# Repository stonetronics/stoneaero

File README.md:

# stoneaero
Flight controller + transmitter hardware using Arduino Nano, NRF24L01, MPU6050, etc

basic transmitter/receiver code is contained in these folders:

* transmitter
  * basic joystick operation
  * throttle on potentiometer

* receiver
  * basic servo signal forwarding from rf module
  * automatic throttle cut and circular descent when there is no signal received for 1.5s

more advanced functions are contained in receevur/trunsmeetur

* hw
  * eagle files for both pcbs
  * receevur
    * ATmega328p
    * 7 servo channels
    * 3S lipo voltage measurement
    * current measurement
    * MPU9250/MPU6050 header
    * NRF24L01+PA+LNA module
  * trunsmeetur
    * Arduino Mega
    * 16x2 generic lcd
    * buttons for lcd menu
    * NRF24L01+PA+LNA module
    * pinheaders for connecting joysticks, switches etc
    * designed to replace the electronics on a "modelcraft N-6" transmitter

* receevur
  * servo signals
    * airbrake mode for ailerons
  * current/voltage reporting

* trunsmeetur
  * lcd display
    * current/voltage report display
    * joystick settings
  * controls for servo signals

feel free to edit

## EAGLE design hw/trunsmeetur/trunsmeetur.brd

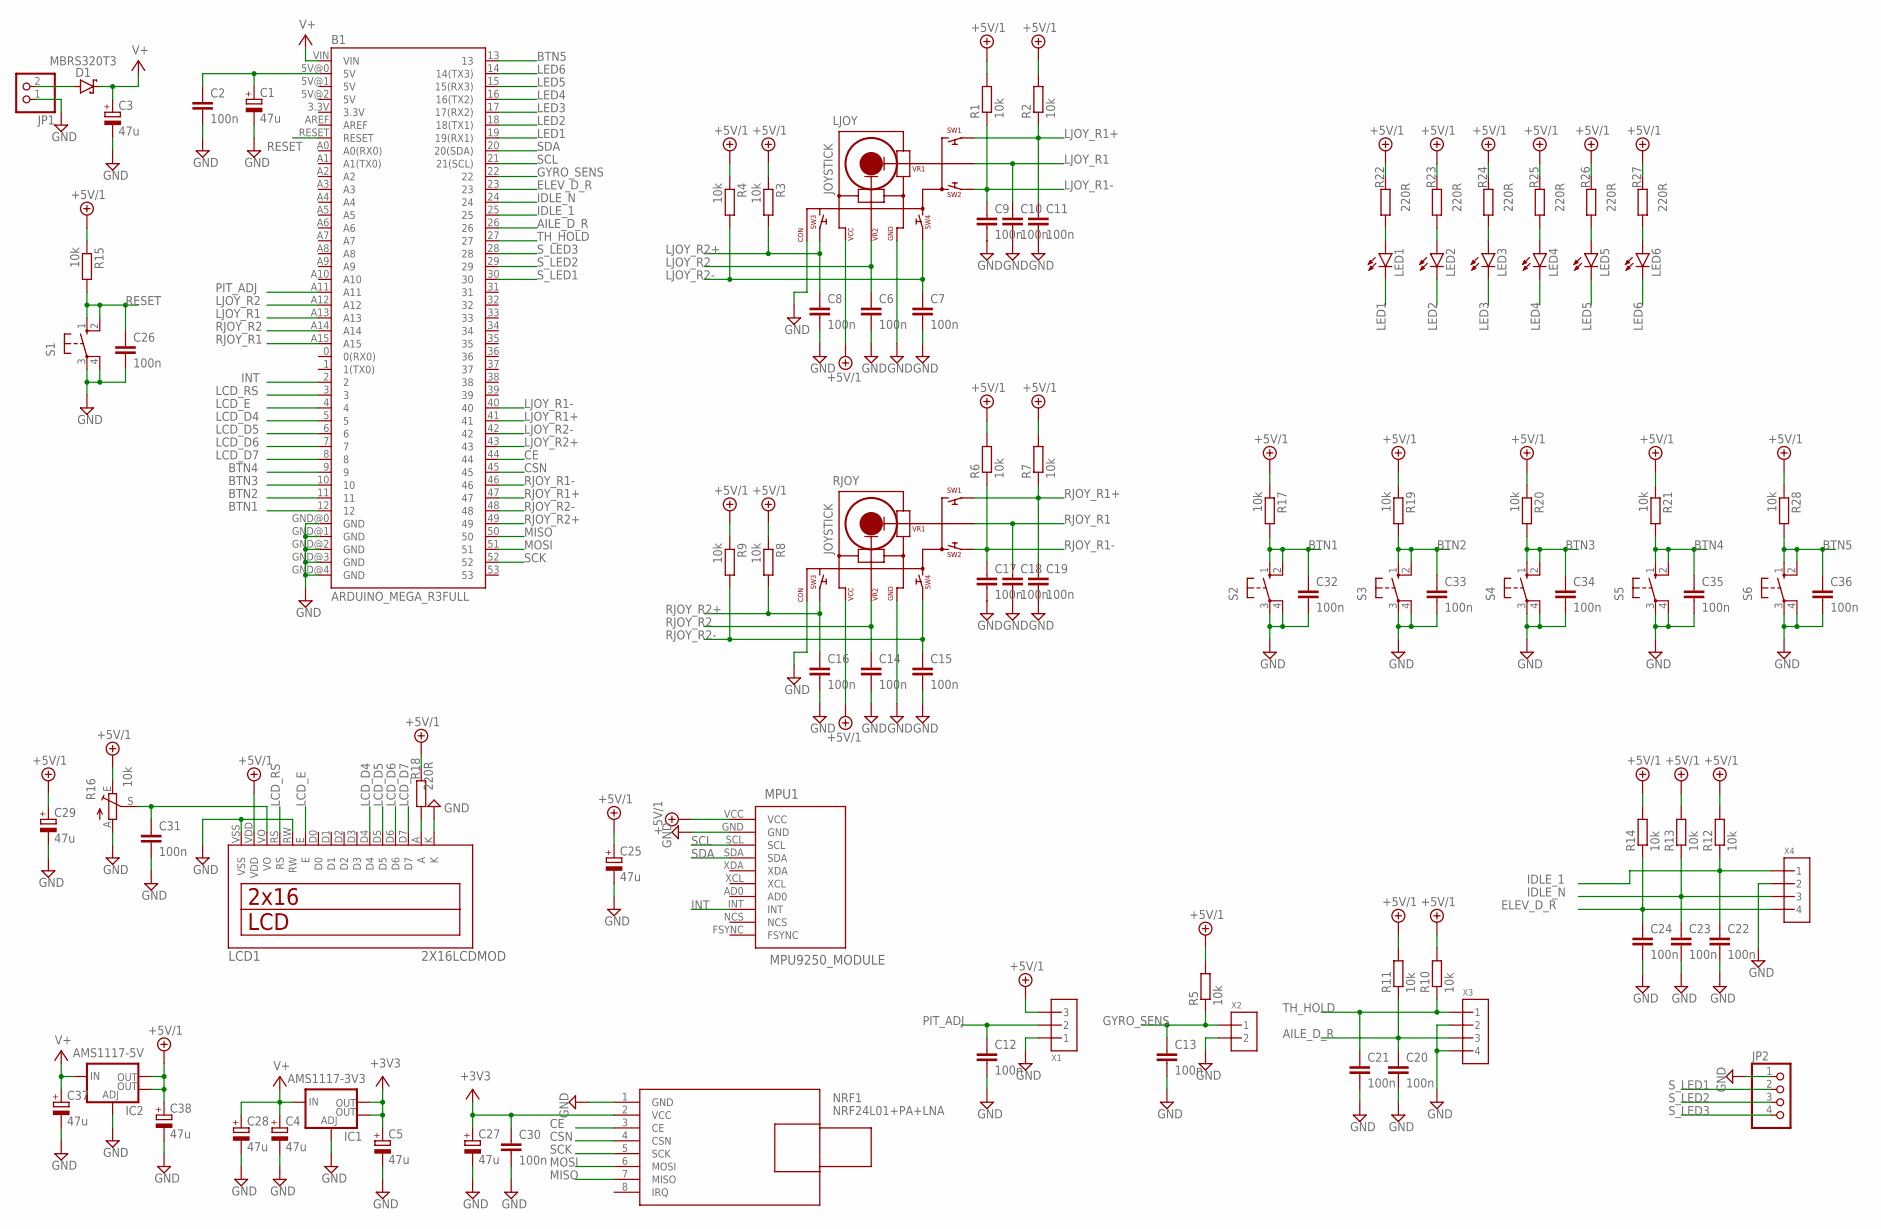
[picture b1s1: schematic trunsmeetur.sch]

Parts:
B1: ARDUINO_MEGA_R3FULL; ARDUINO_MEGA
C1, C3, C4, C5, C25, C27, C28, C29, C37, C38: 47u; 153CLV-0605
C2, C6, C7, C8, C9, C10, C11, C12, C13, C14, C15, C16, C17, C18, C19, C20, C21, C22, C23, C24, C26, C30, C31, C32, C33, C34, C35, C36: 100n; C0805
D1: MBRS320T3; SMC
IC1: AMS1117-3V3; SOT223
IC2: AMS1117-5V; SOT223
JP1: PINHD-1X2; 1X02
JP2: PINHD-1X4; 1X04
LCD1: 2X16LCDMOD; LCD16X2MOD
LED1, LED2, LED3, LED4, LED5, LED6: LEDCHIPLED_0805; CHIPLED_0805
LJOY: JOYSTICK; JOYSTICKCONNECTOR
MPU1: MPU9250_MODULE
NRF1: NRF24L01+PA+LNA; WIRELESS-NRF24L01-PA-EXT
R1, R2, R3, R4, R5, R6, R7, R8, R9, R10, R11, R12, R13, R14, R15, R17, R19, R20, R21, R28: 10k; M0805
R16: 10k; CA9V
R18, R22, R23, R24, R25, R26, R27: 220R; M0805
RJOY: JOYSTICK; JOYSTICKCONNECTOR
S1, S2, S3, S4, S5, S6: 10-XX; B3F-10XX
X1: 3PIN; 3PINCONNECTOR
X2: 2PIN; 2PINCONNECTOR
X3, X4: 4PIN; 4PINCONNECTOR

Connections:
+3V3: C5.+, C27.+, C30.1, IC1.2 (OUT), IC1.4 (OUT), NRF1.2 (VCC)
+5V/1: C25.+, C29.+, C38.+, IC2.2 (OUT), IC2.4 (OUT), LCD1.VDD, LJOY.VCC, MPU1.VCC, R1.2, R2.2, R3.1, R4.1, R5.2, R6.2, R7.2, R8.1, R9.1, R10.2, R11.2, R12.2, R13.2, R14.2, R15.1, R16.E, R17.1, R18.1, R19.1, R20.1, R21.1, R22.1, R23.1, R24.1, R25.1, R26.1, R27.1, R28.1, RJOY.VCC, X1.3
AILE_D_R: B1.26, C20.1, R11.1, X3.3
BTN1: B1.12, C32.1, R17.2, S2.1 (S), S2.2 (S1)
BTN2: B1.11, C33.1, R19.2, S3.1 (S), S3.2 (S1)
BTN3: B1.10, C34.1, R20.2, S4.1 (S), S4.2 (S1)
BTN4: B1.9, C35.1, R21.2, S5.1 (S), S5.2 (S1)
BTN5: B1.13, C36.1, R28.2, S6.1 (S), S6.2 (S1)
CE: B1.44, NRF1.3 (CE)
CSN: B1.45, NRF1.4 (CSN)
ELEV_D_R: B1.23, C24.1, R14.1, X4.4
GND: B1.GND@0 (GND), B1.GND@1 (GND), B1.GND@2 (GND), B1.GND@3 (GND), B1.GND@4 (GND), C1.-, C2.2, C3.-, C4.-, C5.-, C6.2, C7.2, C8.2, C9.2, C10.2, C11.2, C12.2, C13.2, C14.2, C15.2, C16.2, C17.2, C18.2, C19.2, C20.2, C21.2, C22.2, C23.2, C24.2, C25.-, C26.2, C27.-, C28.-, C29.-, C30.2, C31.2, C32.2, C33.2, C34.2, C35.2, C36.2, C37.-, C38.-, IC1.1 (ADJ), IC2.1 (ADJ), JP1.1, JP2.1, LCD1.K, LCD1.RW, LCD1.VSS, LJOY.CON, LJOY.GND, MPU1.GND, NRF1.1 (GND), R16.A, RJOY.CON, RJOY.GND, S1.3, S1.4 (P1), S2.3, S2.4 (P1), S3.3, S3.4 (P1), S4.3, S4.4 (P1), S5.3, S5.4 (P1), S6.3, S6.4 (P1), X1.1, X2.2, X3.2, X3.4, X4.2
GYRO_SENS: B1.22, C13.1, R5.1, X2.1
IDLE_1: B1.25, C22.1, R12.1, X4.1
IDLE_N: B1.24, C23.1, R13.1, X4.3
INT: B1.2, MPU1.INT
LCD_D4: B1.5, LCD1.D4
LCD_D5: B1.6, LCD1.D5
LCD_D6: B1.7, LCD1.D6
LCD_D7: B1.8, LCD1.D7
LCD_E: B1.4, LCD1.E
LCD_RS: B1.3, LCD1.RS
LED1: B1.19 (19(RX1)), LED1.C
LED2: B1.18 (18(TX1)), LED2.C
LED3: B1.17 (17(RX2)), LED3.C
LED4: B1.16 (16(TX2)), LED4.C
LED5: B1.15 (15(RX3)), LED5.C
LED6: B1.14 (14(TX3)), LED6.C
LJOY_R1: B1.A13, C10.1, LJOY.VR1
LJOY_R1+: B1.41, C11.1, LJOY.SW1, R2.1
LJOY_R1-: B1.40, C9.1, LJOY.SW2, R1.1
LJOY_R2: B1.A12, C6.1, LJOY.VR2
LJOY_R2+: B1.43, C8.1, LJOY.SW3, R3.2
LJOY_R2-: B1.42, C7.1, LJOY.SW4, R4.2
MISO: B1.50, NRF1.7 (MISO)
MOSI: B1.51, NRF1.6 (MOSI)
unnamed: C31.1, LCD1.VO, R16.S
unnamed: D1.A, JP1.2
unnamed: LCD1.A, R18.2
unnamed: LED1.A, R22.2
unnamed: LED2.A, R23.2
unnamed: LED3.A, R24.2
unnamed: LED4.A, R25.2
unnamed: LED5.A, R26.2
unnamed: LED6.A, R27.2
unnamed: B1.5V@0 (5V), C1.+, C2.1
PIT_ADJ: B1.A11, C12.1, X1.2
RESET: B1.RESET, C26.1, R15.2, S1.1 (S), S1.2 (S1)
RJOY_R1: B1.A15, C18.1, RJOY.VR1
RJOY_R1+: B1.47, C19.1, R7.1, RJOY.SW1
RJOY_R1-: B1.46, C17.1, R6.1, RJOY.SW2
RJOY_R2: B1.A14, C14.1, RJOY.VR2
RJOY_R2+: B1.49, C16.1, R8.2, RJOY.SW3
RJOY_R2-: B1.48, C15.1, R9.2, RJOY.SW4
SCK: B1.52, NRF1.5 (SCK)
SCL: B1.21 (21(SCL)), MPU1.SCL
SDA: B1.20 (20(SDA)), MPU1.SDA
S_LED1: B1.30, JP2.2
S_LED2: B1.29, JP2.3
S_LED3: B1.28, JP2.4
TH_HOLD: B1.27, C21.1, R10.1, X3.1
V+: B1.VIN, C3.+, C4.+, C28.+, C37.+, D1.C, IC1.3 (IN), IC2.3 (IN)

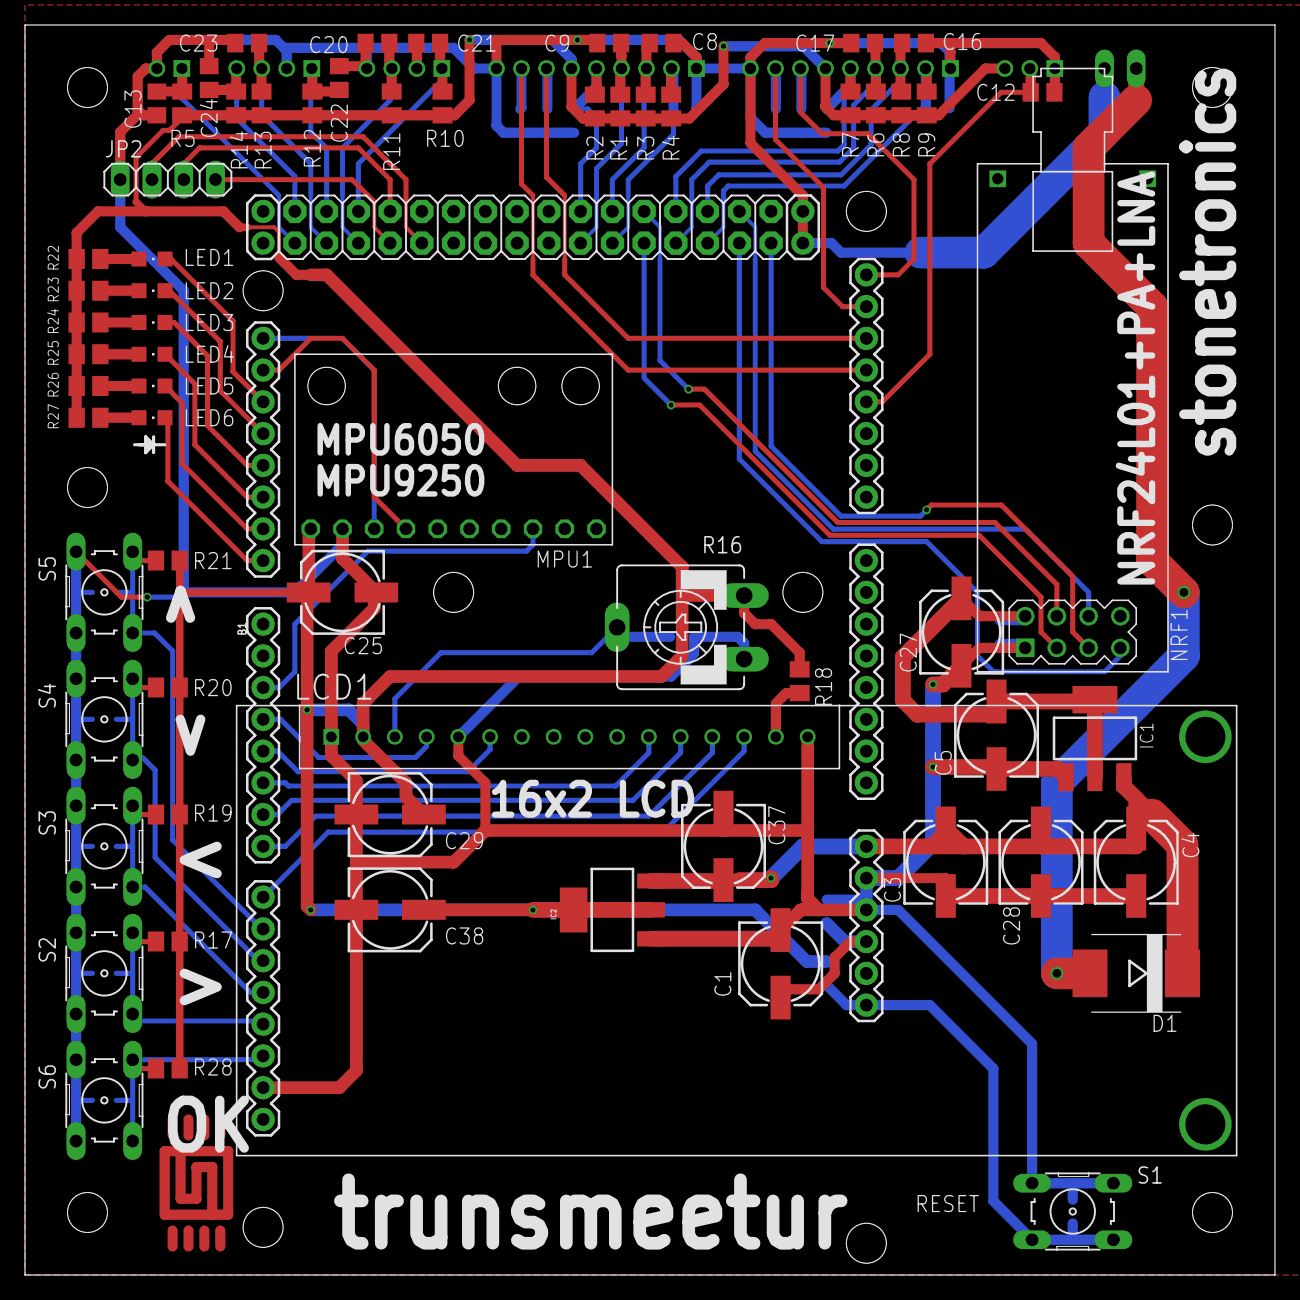
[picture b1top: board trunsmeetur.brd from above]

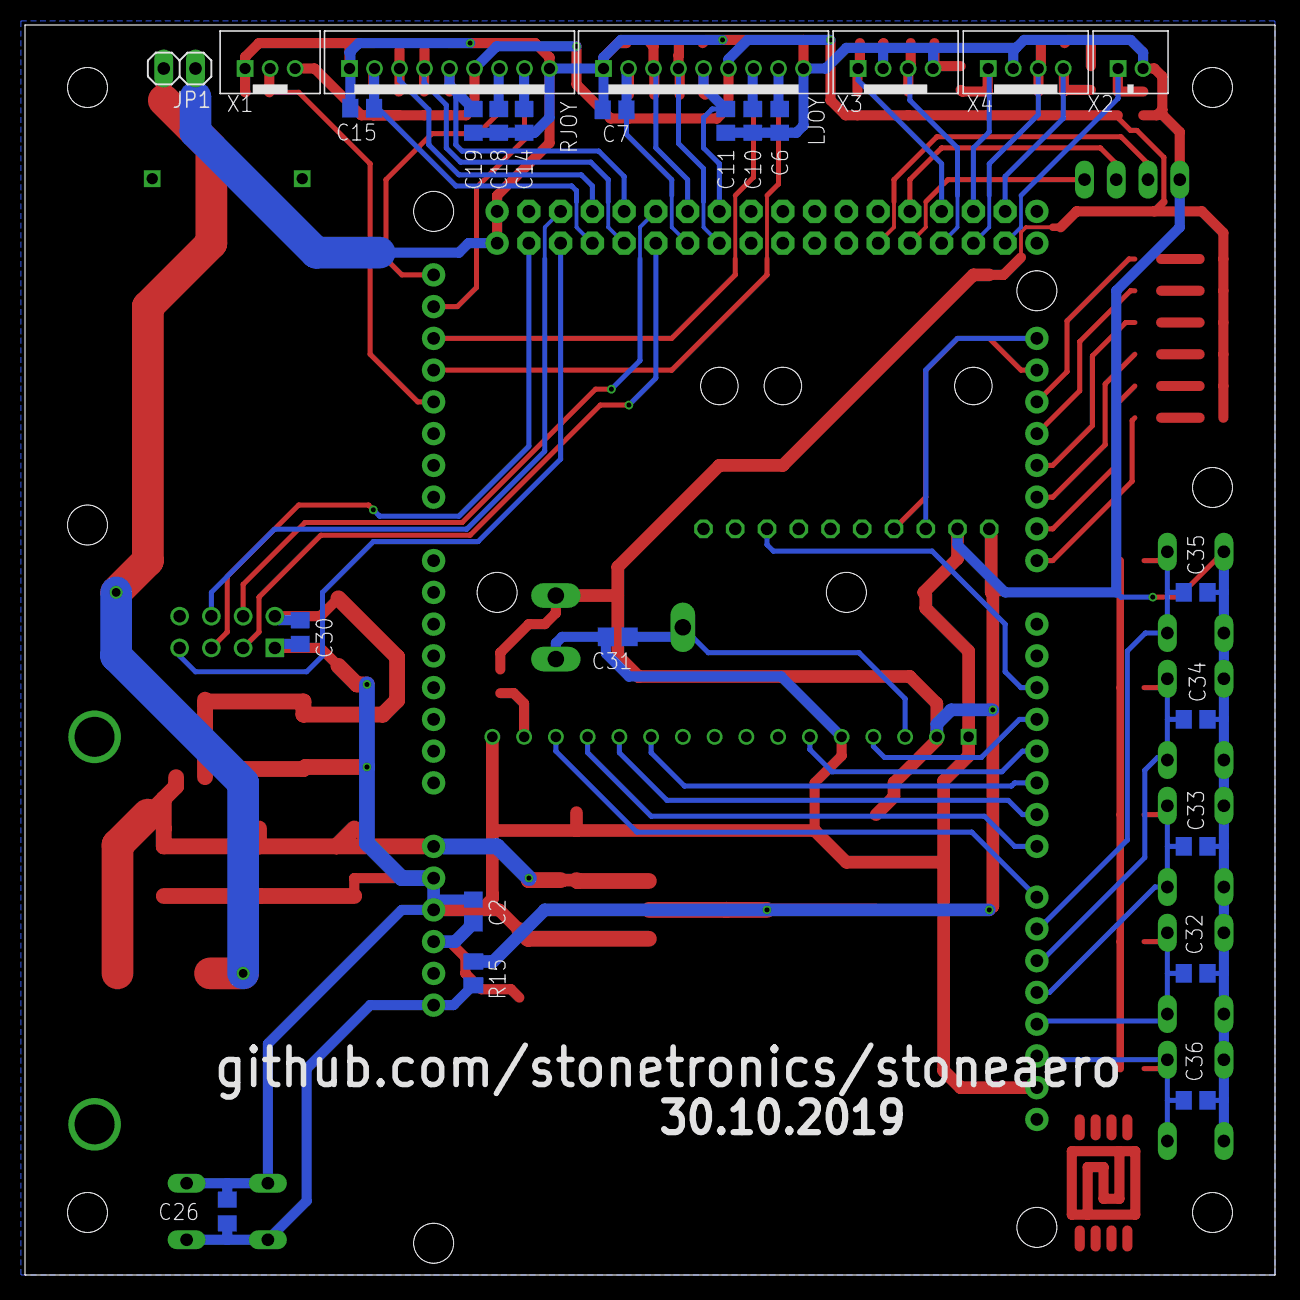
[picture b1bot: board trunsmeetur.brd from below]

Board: 2 copper layers, 100.0 x 100.0 mm, 93 parts (25 on the bottom side), 62 nets.

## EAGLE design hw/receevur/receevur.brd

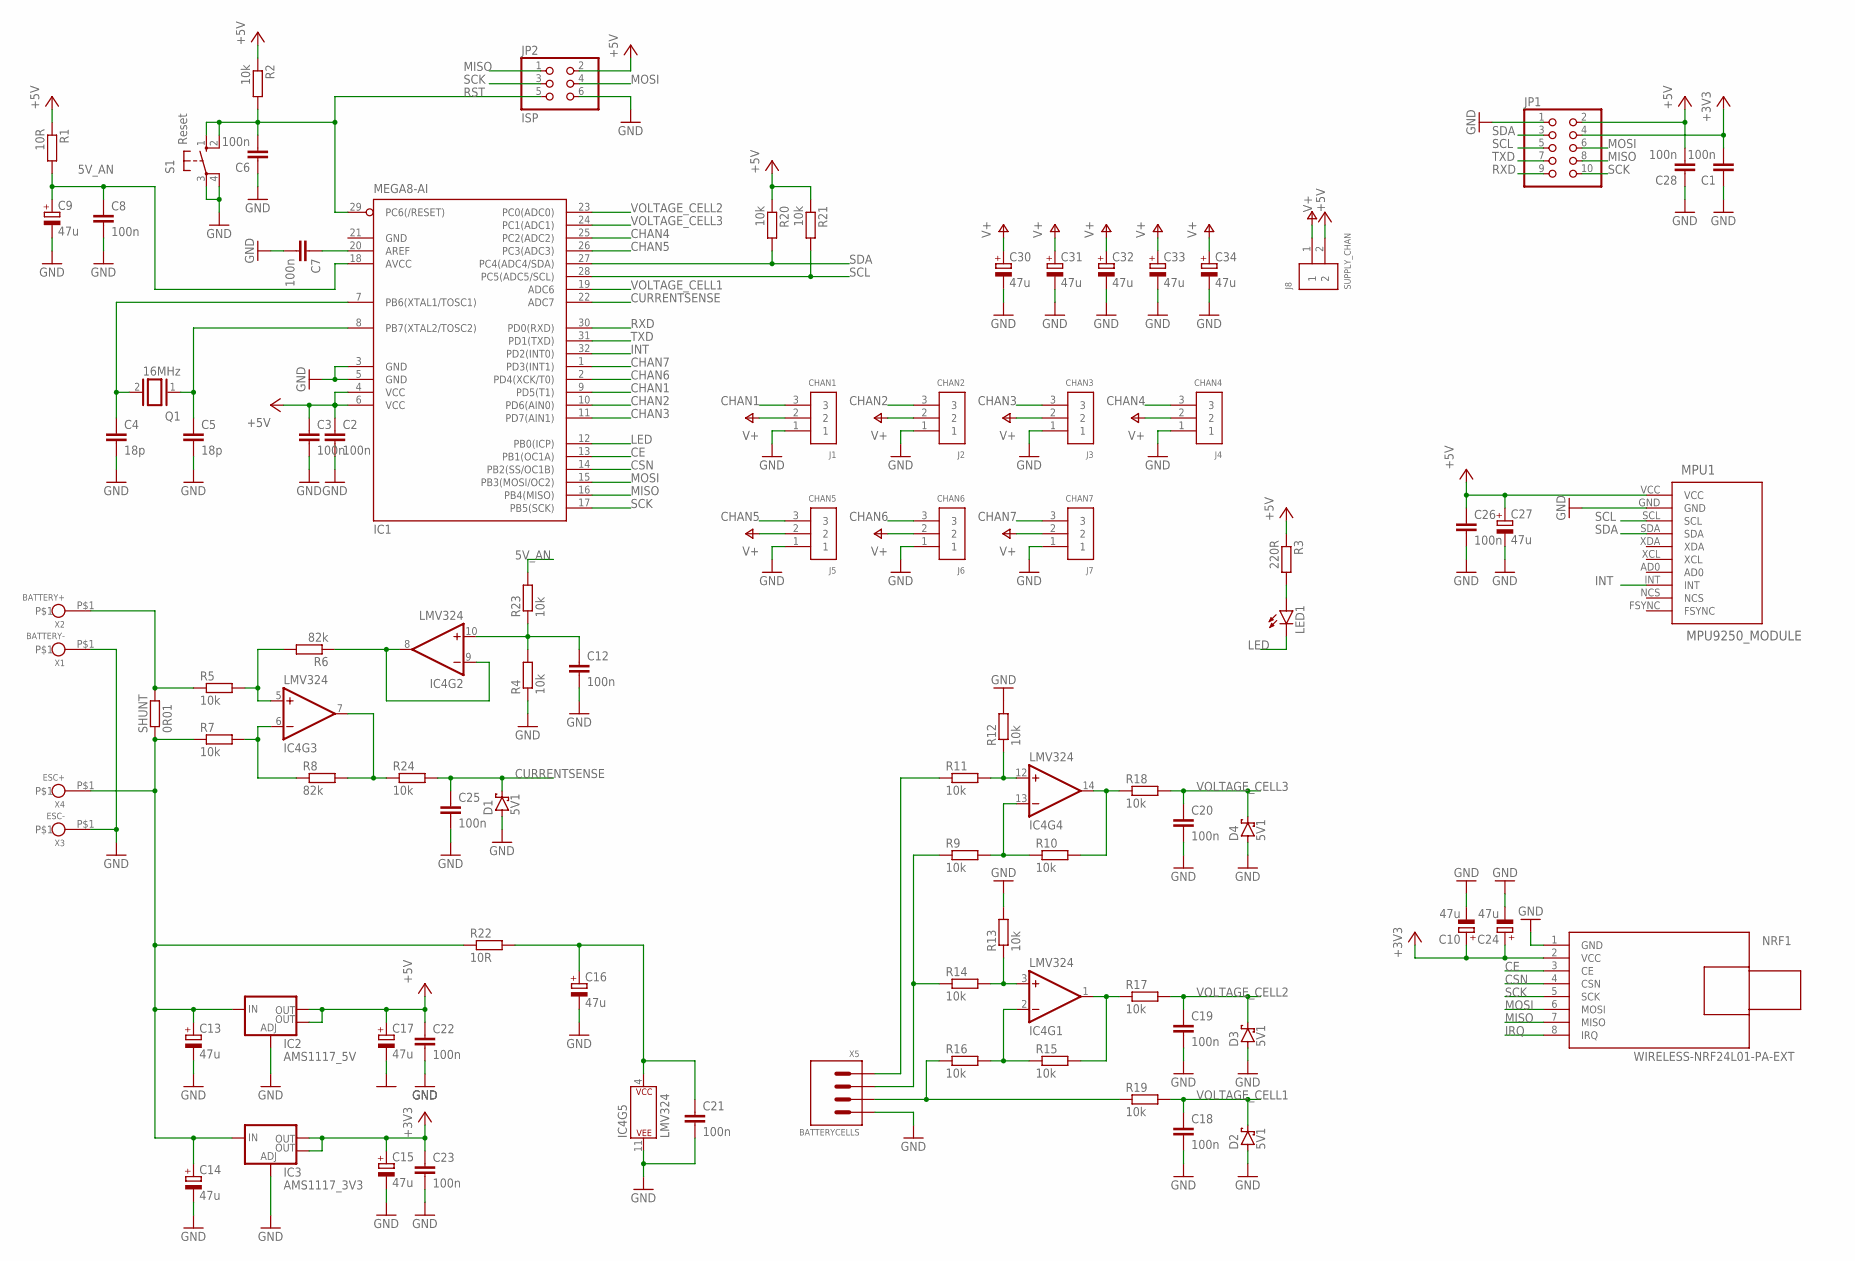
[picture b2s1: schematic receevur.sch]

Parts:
C1, C2, C3, C6, C7, C8, C12, C18, C19, C20, C21, C22, C23, C25, C26, C28: 100n; C0805
C4, C5: 18p; C0805
C9, C10, C13, C14, C15, C16, C17, C24, C27, C30, C31, C32, C33, C34: 47u; 153CLV-0405
D1, D2, D3, D4: 5V1; SOD323_ST
IC1: MEGA8-AI; TQFP32-08
IC2: AMS1117_5V; SOT223
IC3: AMS1117_3V3; SOT223
IC4: LMV324; SO14
J1: CHAN1; 61300311121
J2: CHAN2; 61300311121
J3: CHAN3; 61300311121
J4: CHAN4; 61300311121
J5: CHAN5; 61300311121
J6: CHAN6; 61300311121
J7: CHAN7; 61300311121
J8: SUPPLY_CHAN; 61300211121
JP1: PINHD-2X5; 2X05
JP2: ISP; 2X03
LED1: LEDCHIP-LED0805; CHIP-LED0805
MPU1: MPU9250_MODULE
NRF1: WIRELESS-NRF24L01-PA-EXT
Q1: 16MHz; QS
R1, R22: 10R; R0805
R2, R4, R5, R7, R9, R10, R11, R12, R13, R14, R15, R16, R17, R18, R19, R20, R21, R23, R24: 10k; R0805
R3: 220R; R0805
R6, R8: 82k; R0805
S1: Reset; B3F-10XX
SHUNT: 0R01; R2512
X1: BATTERY-; SMDSOLDERPAD_5X7
X2: BATTERY+; SMDSOLDERPAD_5X7
X3: ESC-; SMDSOLDERPAD_5X7
X4: ESC+; SMDSOLDERPAD_5X7
X5: BATTERYCELLS; CELLJACK

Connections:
5V_AN: C8.1, C9.+, IC1.18 (AVCC), R1.2, R23.2
+3V3: C1.2, C10.+, C15.+, C23.1, C24.+, IC3.2 (OUT), IC3.4 (OUT), JP1.4, NRF1.2 (VCC)
+5V: C2.1, C3.1, C17.+, C22.1, C26.1, C27.+, C28.2, IC1.4 (VCC), IC1.6 (VCC), IC2.2 (OUT), IC2.4 (OUT), J8.2, JP1.2, JP2.2, MPU1.VCC, R1.1, R2.1, R3.1, R20.1, R21.1
CE: IC1.13 (PB1(OC1A)), NRF1.3 (CE)
CHAN1: IC1.9 (PD5(T1)), J1.3
CHAN2: IC1.10 (PD6(AIN0)), J2.3
CHAN3: IC1.11 (PD7(AIN1)), J3.3
CHAN4: IC1.25 (PC2(ADC2)), J4.3
CHAN5: IC1.26 (PC3(ADC3)), J5.3
CHAN6: IC1.2 (PD4(XCK/T0)), J6.3
CHAN7: IC1.1 (PD3(INT1)), J7.3
CSN: IC1.14 (PB2(SS/OC1B)), NRF1.4 (CSN)
CURRENTSENSE: C25.1, D1.C, IC1.22 (ADC7), R24.2
GND: C1.1, C2.2, C3.2, C4.2, C5.2, C6.1, C7.2, C8.2, C9.-, C10.-, C12.2, C13.-, C14.-, C15.-, C16.-, C17.-, C18.2, C19.2, C20.2, C21.2, C22.2, C23.2, C24.-, C25.2, C26.2, C27.-, C28.1, C30.-, C31.-, C32.-, C33.-, C34.-, D1.A, D2.A, D3.A, D4.A, IC1.3 (GND), IC1.5 (GND), IC1.21 (GND), IC2.1 (ADJ), IC3.1 (ADJ), IC4.11 (P$V-), J1.1, J2.1, J3.1, J4.1, J5.1, J6.1, J7.1, JP1.1, JP2.6, MPU1.GND, NRF1.1 (GND), R4.1, R12.2, R13.2, S1.3, S1.4 (P1), X1.P$1, X3.P$1, X5.P$1
INT: IC1.32 (PD2(INT0)), MPU1.INT
IRQ: NRF1.8 (IRQ)
LED: IC1.12 (PB0(ICP)), LED1.C
MISO: IC1.16 (PB4(MISO)), JP1.8, JP2.1, NRF1.7 (MISO)
MOSI: IC1.15 (PB3(MOSI/OC2)), JP1.6, JP2.4, NRF1.6 (MOSI)
unnamed: C4.1, IC1.7 (PB6(XTAL1/TOSC1)), Q1.2
unnamed: C5.1, IC1.8 (PB7(XTAL2/TOSC2)), Q1.1
unnamed: C7.1, IC1.20 (AREF)
unnamed: LED1.A, R3.2
unnamed: C13.+, C14.+, IC2.3 (IN), IC3.3 (IN), R7.1, R22.1, SHUNT.1, X4.P$1
unnamed: IC4.12 (+IN), R11.2, R12.1
unnamed: C16.+, C21.1, IC4.4 (P$V+), R22.2
unnamed: R5.1, SHUNT.2, X2.P$1
unnamed: IC4.13 (-IN), R9.2, R10.1
unnamed: IC4.8 (OUT), IC4.9 (-IN), R6.1
unnamed: IC4.6 (-IN), R7.2, R8.1
unnamed: IC4.14 (OUT), R10.2, R18.1
unnamed: IC4.3 (+IN), R13.1, R14.2
unnamed: IC4.2 (-IN), R15.1, R16.2
unnamed: IC4.1 (OUT), R15.2, R17.1
unnamed: R11.1, X5.P$4
unnamed: R9.1, R14.1, X5.P$3
unnamed: R16.1, R19.1, X5.P$2
unnamed: C12.1, IC4.10 (+IN), R4.2, R23.1
unnamed: IC4.5 (+IN), R5.2, R6.2
N$$$: IC4.7 (OUT), R8.2, R24.1
RST: C6.2, IC1.29 (PC6(/RESET)), JP2.5, R2.2, S1.1 (S), S1.2 (S1)
RXD: IC1.30 (PD0(RXD)), JP1.9
SCK: IC1.17 (PB5(SCK)), JP1.10, JP2.3, NRF1.5 (SCK)
SCL: IC1.28 (PC5(ADC5/SCL)), JP1.5, MPU1.SCL, R21.2
SDA: IC1.27 (PC4(ADC4/SDA)), JP1.3, MPU1.SDA, R20.2
TXD: IC1.31 (PD1(TXD)), JP1.7
V+: C30.+, C31.+, C32.+, C33.+, C34.+, J1.2, J2.2, J3.2, J4.2, J5.2, J6.2, J7.2, J8.1
VOLTAGE_CELL1: C18.1, D2.C, IC1.19 (ADC6), R19.2
VOLTAGE_CELL2: C19.1, D3.C, IC1.23 (PC0(ADC0)), R17.2
VOLTAGE_CELL3: C20.1, D4.C, IC1.24 (PC1(ADC1)), R18.2

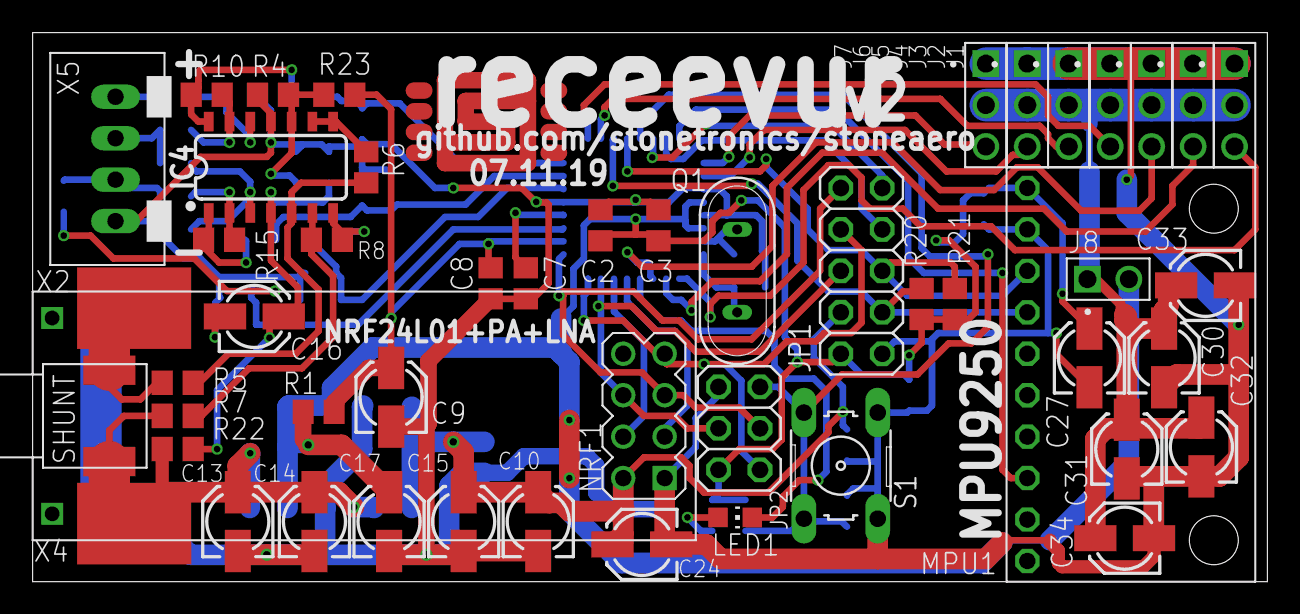
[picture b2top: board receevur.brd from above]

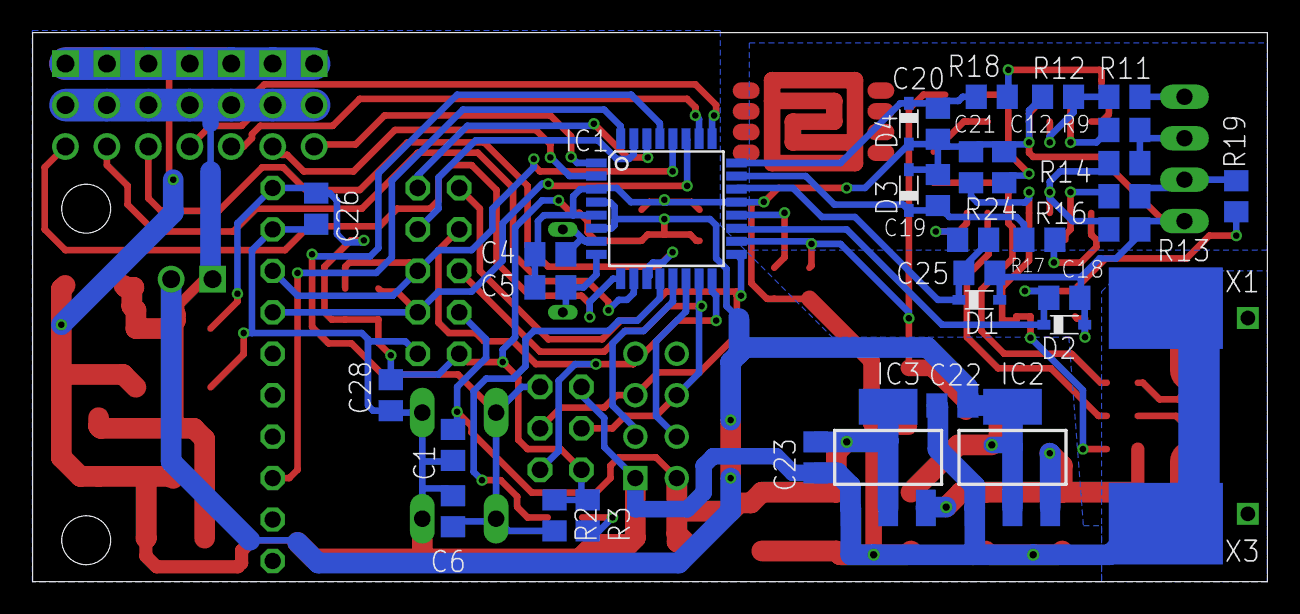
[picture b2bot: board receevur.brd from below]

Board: 2 copper layers, 75.7 x 33.6 mm, 85 parts (35 on the bottom side), 49 nets.

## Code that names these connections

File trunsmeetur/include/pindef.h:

#ifndef __PINDEF_H__
#define __PINDEF_H__


//JOYSTICKS

#define LJOY_R1       A13
#define LJOY_R1PLUS   41
#define LJOY_R1MINUS  40

#define LJOY_R2       A12
#define LJOY_R2PLUS   43
#define LJOY_R2MINUS  42

#define RJOY_R1       A15
#define RJOY_R1PLUS   47
#define RJOY_R1MINUS  46

#define RJOY_R2       A14
#define RJOY_R2PLUS   49
#define RJOY_R2MINUS  48


//PCB BUTTONS

#define BTN1    12
#define BTN2    11
#define BTN3    10
#define BTN4    9
#define BTN5    13

//readability
#define BTN_UP      BTN4
#define BTN_DOWN    BTN3
#define BTN_LEFT    BTN2
#define BTN_RIGHT   BTN1
#define BTN_OK      BTN5


//PCB LEDS (0-active)

#define LED1  19
#define LED2  18
#define LED3  17
#define LED4  16
#define LED5  15
#define LED6  14


//pitch adj poti

#define PIT_ADJ   A11


//finger switches

#define GYRO_SENS   (22)
#define ELEV_D_R    (23)
#define IDLE_N      (24)
#define IDLE_1      (25)
#define AILE_D_R    (26)
#define TH_HOLD     (27)


//case LEDS (1-active)

#define S_LED1    30
#define S_LED2    29
#define S_LED3    28

//readability
#define S_CHARGE  S_LED2
#define S_HACK    S_LED3
#define S_POWER   S_LED1

//nRF24L01+PA+LNA connection

#define CE      44
#define CSN     45


//MPU9250 interrupt line

#define INT     2


//LCD connection

#define LCD_RS    3
#define LCD_E     4
#define LCD_D4    5
#define LCD_D5    6
#define LCD_D6    7
#define LCD_D7    8


#endif

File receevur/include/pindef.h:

#ifndef __PINDEF_H__
#define __PINDEF_H__

////////////////////////////////
/// HARDWARE PIN DEFINITIONS ///
////////////////////////////////

//analog pins
#define VOLTAGE_CELL1   A6
#define VOLTAGE_CELL2   A0
#define VOLATGE_CELL3   A1
#define CURRENTSENSE    A7

//output channels
#define CHAN1 5
#define CHAN2 6
#define CHAN3 7
#define CHAN4 A2
#define CHAN5 A3
#define CHAN6 4
#define CHAN7 3

//mpu interface
#define INT 2

//nRF24L01+ interface
#define CE    9
#define CSN   10

//LED
#define LED   8

#endif

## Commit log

2019-06-09 basic transmitter/receiver pair
2019-06-13 add servo rate control to transmitter
2020-01-18 add pcb files and better firmware
2020-01-18 cleanup

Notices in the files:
parts and their libraries:
SparkFun-IC-Power: Licensing: Creative Commons ShareAlike 4.0 International - https://creativecommons.org/licenses/by-sa/4.0
diy-modules: Released under the Creative Commons Attribution 4.0 International License: http://creativecommons.org/licenses/by/4.0
